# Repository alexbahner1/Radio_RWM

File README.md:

# Radio_RWM

# Example folder - has code examples 

# PCB folder - has the KICAD files

# Radio F - is the final version of the firmware 

# Rev1 - is other versionor Frimware not stable

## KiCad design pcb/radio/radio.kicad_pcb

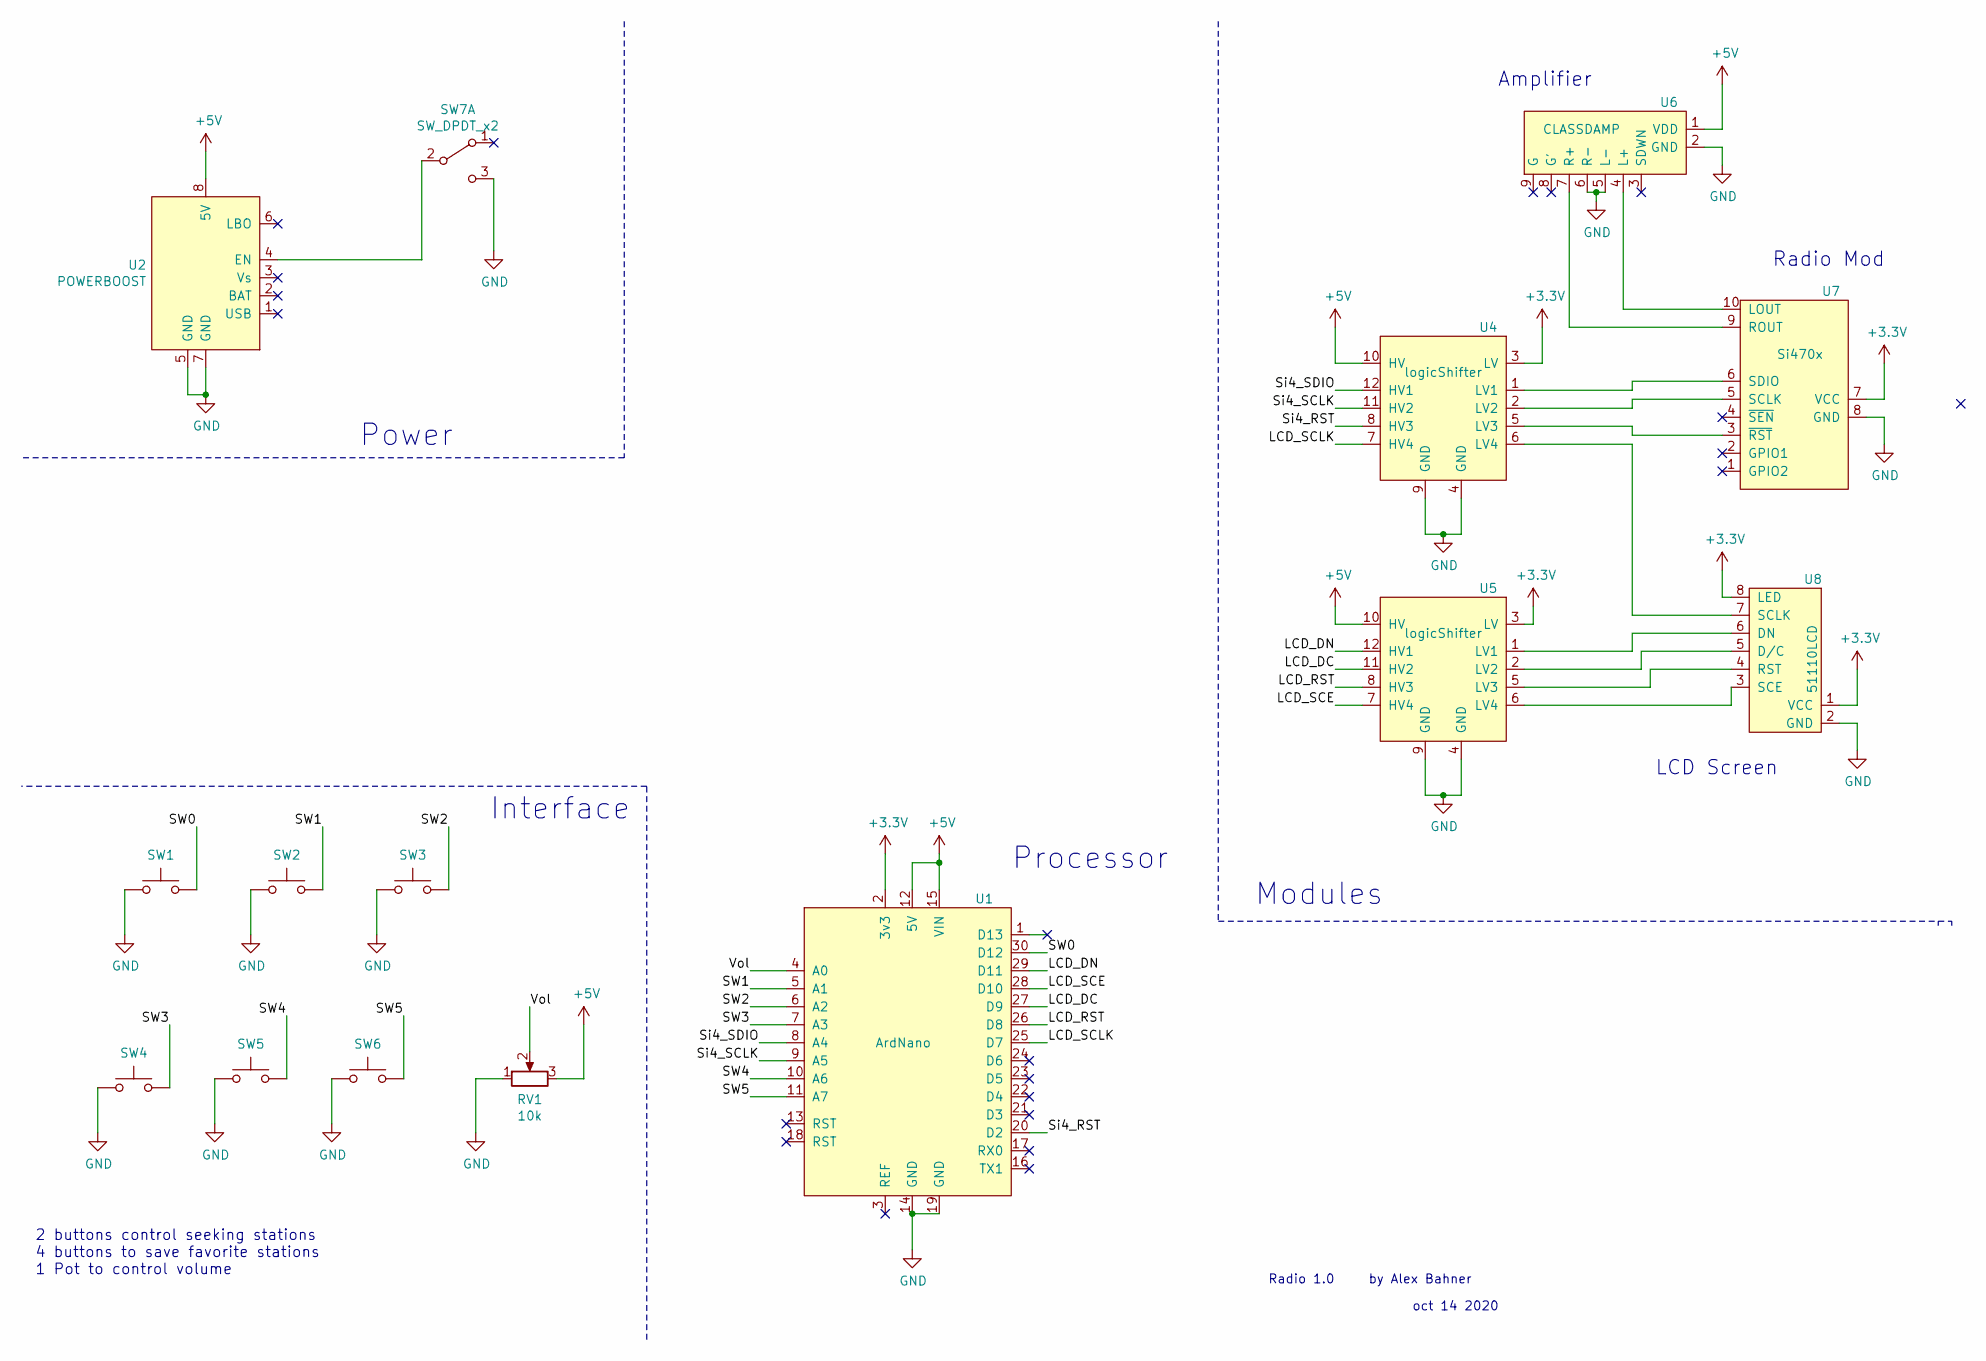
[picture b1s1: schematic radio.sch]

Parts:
RV1: 10k; Potentiometer_Alps_RK163_Single_Horizontal
SW1, SW2, SW3, SW4, SW5, SW6: SW_Push; SW_PUSH_6mm_H4.3mm
SW7: SW_DPDT_x2; EG1218
U1: ArdNano; MODULE_A000005
U2: POWERBOOST; PinSocket_1x08_powerboost
U4, U5: logicShifter; PinSocket_1x06_logicshift
U6: CLASSDAMP; PinSocket_1x09_cldAMP
U7: Si470x; PinSocket_1x10_P2.54mm_Vertical
U8: 51110LCD; PinSocket_1x08_nokiaLCD

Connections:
+3V3: U1.2 (3v3), U4.3 (LV), U5.3 (LV), U7.7 (VCC), U8.1 (VCC), U8.8 (LED)
+5V: RV1.3, U1.12 (5V), U1.15 (VIN), U2.8 (5V), U4.10 (HV), U5.10 (HV), U6.1 (VDD)
/LCD_DC: U1.27 (D9), U5.11 (HV2)
/LCD_DN: U1.29 (D11), U5.12 (HV1)
/LCD_RST: U1.26 (D8), U5.8 (HV3)
/LCD_SCE: U1.28 (D10), U5.7 (HV4)
/LCD_SCLK: U1.25 (D7), U4.7 (HV4)
/SW0: SW1.2, U1.30 (D12)
/SW1: SW2.2, U1.5 (A1)
/SW2: SW3.2, U1.6 (A2)
/SW3: SW4.2, U1.7 (A3)
/SW4: SW5.2, U1.10 (A6)
/SW5: SW6.2, U1.11 (A7)
/Si4_RST: U1.20 (D2), U4.8 (HV3)
/Si4_SCLK: U1.9 (A5), U4.11 (HV2)
/Si4_SDIO: U1.8 (A4), U4.12 (HV1)
/Vol: RV1.2, U1.4 (A0)
GND: RV1.1, SW1.1, SW2.1, SW3.1, SW4.1, SW5.1, SW6.1, SW7.3 (C), U1.14 (GND), U1.19 (GND), U2.5 (GND), U2.7 (GND), U4.4 (GND), U4.9 (GND), U5.4 (GND), U5.9 (GND), U6.2 (GND), U6.5 (L-), U6.6 (R-), U7.8 (GND), U8.2 (GND)
unnamed: SW7.2 (B), U2.4 (EN)
unnamed: U4.1 (LV1), U7.6 (SDIO)
unnamed: U4.2 (LV2), U7.5 (SCLK)
unnamed: U4.5 (LV3), U7.3 (~RST)
unnamed: U4.6 (LV4), U8.7 (SCLK)
unnamed: U5.1 (LV1), U8.6 (DN)
unnamed: U5.2 (LV2), U8.5 (D/C)
unnamed: U5.5 (LV3), U8.4 (RST)
unnamed: U5.6 (LV4), U8.3 (SCE)
unnamed: U6.4 (L+), U7.10 (LOUT)
unnamed: U6.7 (R+), U7.9 (ROUT)

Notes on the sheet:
oct 14 2020
Radio 1.0 by Alex Bahner
Power
Modules
LCD Screen
Radio Mod
Amplifier
Interface
2 buttons control seeking stations 4 buttons to save favorite stations 1 Pot to control volume
Processor

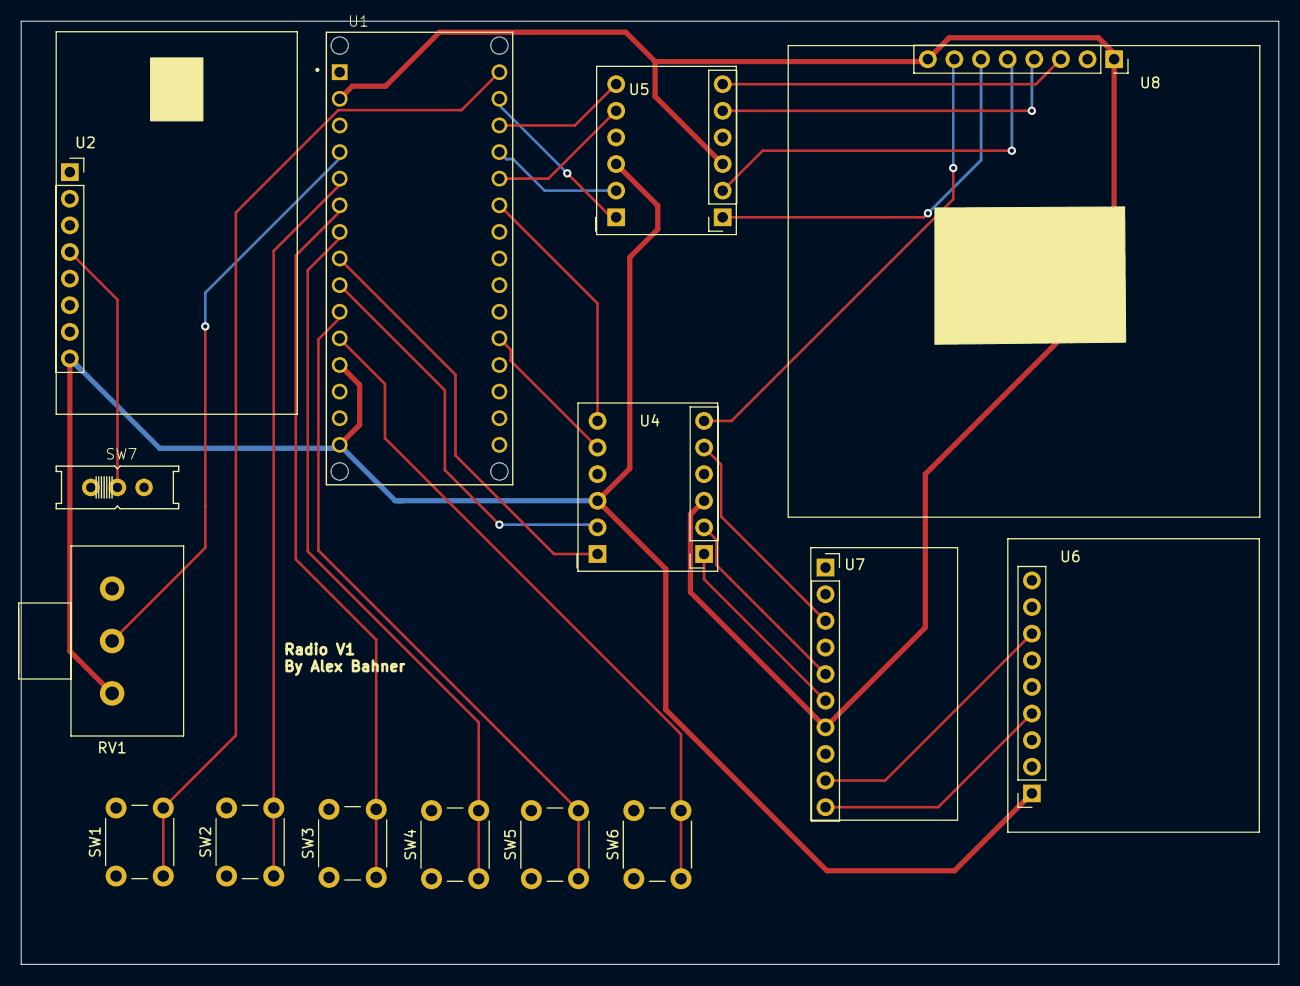
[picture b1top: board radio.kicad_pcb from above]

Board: 2 copper layers, 120.0 x 90.0 mm, 15 parts (0 on the bottom side), 29 nets.

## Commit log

2020-12-19 pushing files
